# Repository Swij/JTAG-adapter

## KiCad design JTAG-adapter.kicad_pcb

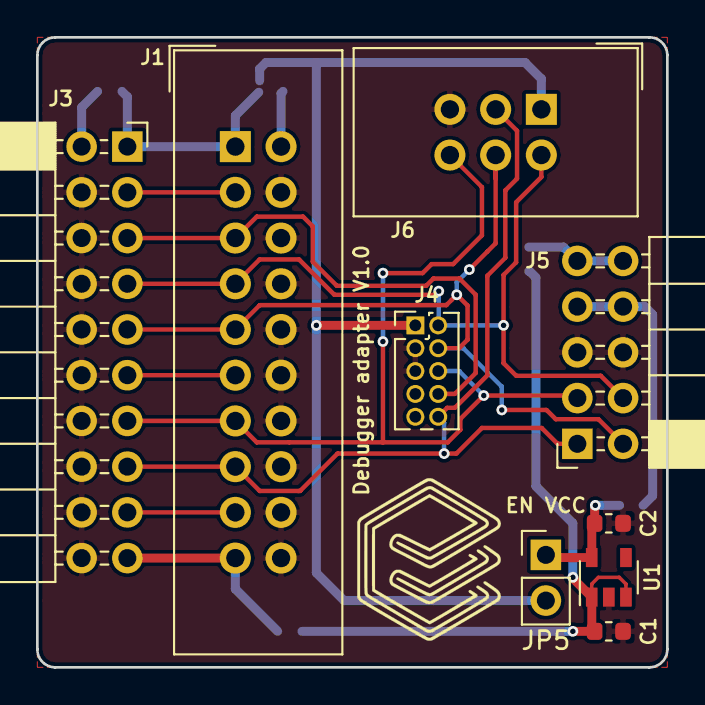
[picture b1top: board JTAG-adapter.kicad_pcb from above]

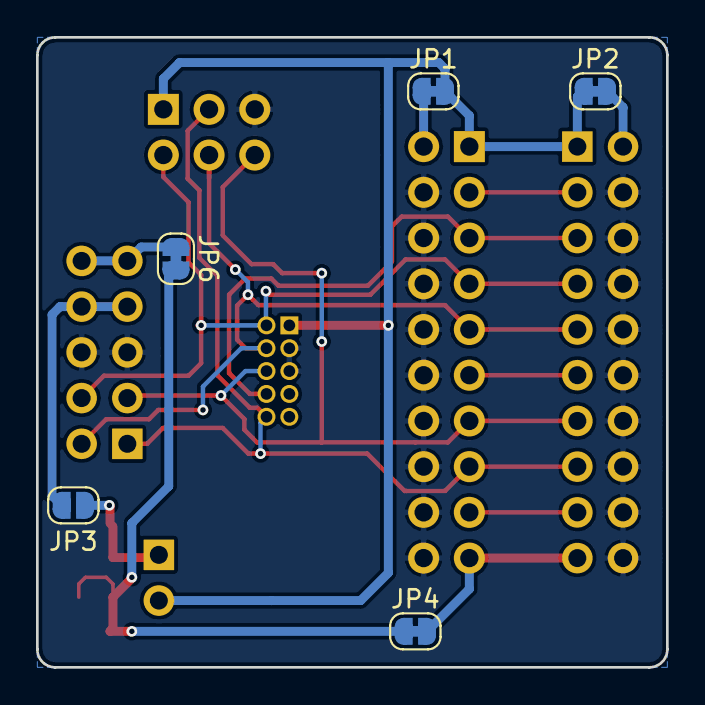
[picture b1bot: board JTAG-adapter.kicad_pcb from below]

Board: 2 copper layers, 35.0 x 35.0 mm, 14 parts (5 on the bottom side), 17 nets.

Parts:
C1, C2: 1u; C_0603_1608Metric
J1: 20-pin JTAG 0.1"; IDC-Header_2x10_P2.54mm_Vertical
J3: 20-pin JTAG 0.1"; PinSocket_2x10_P2.54mm_Horizontal
J4: 10-pin JTAG 0.05"; PinHeader_2x05_P1.27mm_Vertical
J5: 10-pin ST-Link 0.1"; PinSocket_2x05_P2.54mm_Horizontal
J6: 6-pin Tag-Connect; IDC-Header_2x03_P2.54mm_Vertical
JP1, JP2, JP4, JP6: SolderJumper-2_P1.3mm_Bridged_RoundedPad1.0x1.5mm
JP3: SolderJumper-2_P1.3mm_Open_RoundedPad1.0x1.5mm
JP5: PinHeader_1x02_P2.54mm_Vertical
U1: MIC5504-3.3YM5; SOT-23-5

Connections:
+3V3: C2.1, JP3.2, JP5.1, U1.5
+5V: C1.2, JP4.2, JP6.2, U1.1, U1.3
/DBACK: J1.19, J3.19, JP4.1
/DBGRQ: J1.17, J3.17
/RTCK: J1.11, J3.11
/ST-Link_3V3: J5.7, J5.8, JP3.1
/ST-Link_5V: J5.9, J5.10, JP6.1
/SWDCLK: J1.9, J3.9, J4.4, J5.2, J6.4
/SWDIO: J1.7, J3.7, J4.2, J5.4, J6.2
/SWIM: J1.13, J3.13, J4.6, J5.3, J6.6
/TDI: J1.5, J3.5, J4.8
/TRST: J1.3, J3.3
/VCC: J1.1, J3.1, J4.1, J6.1, JP1.2, JP2.2, JP5.2
/nRESET: J1.15, J3.15, J4.10, J5.1, J6.3
GND: C1.1, C2.2, J1.4, J1.6, J1.8, J1.10, J1.12, J1.14, J1.16, J1.18, J1.20, J3.4, J3.6, J3.8, J3.10, J3.12, J3.14, J3.16, J3.18, J3.20, J4.3, J4.5, J5.5, J5.6, J6.5, U1.2
unnamed: J1.2, JP1.1
unnamed: J3.2, JP2.1

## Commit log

2019-01-16 Draft of schematic and layout
2019-08-30 WIP commit
